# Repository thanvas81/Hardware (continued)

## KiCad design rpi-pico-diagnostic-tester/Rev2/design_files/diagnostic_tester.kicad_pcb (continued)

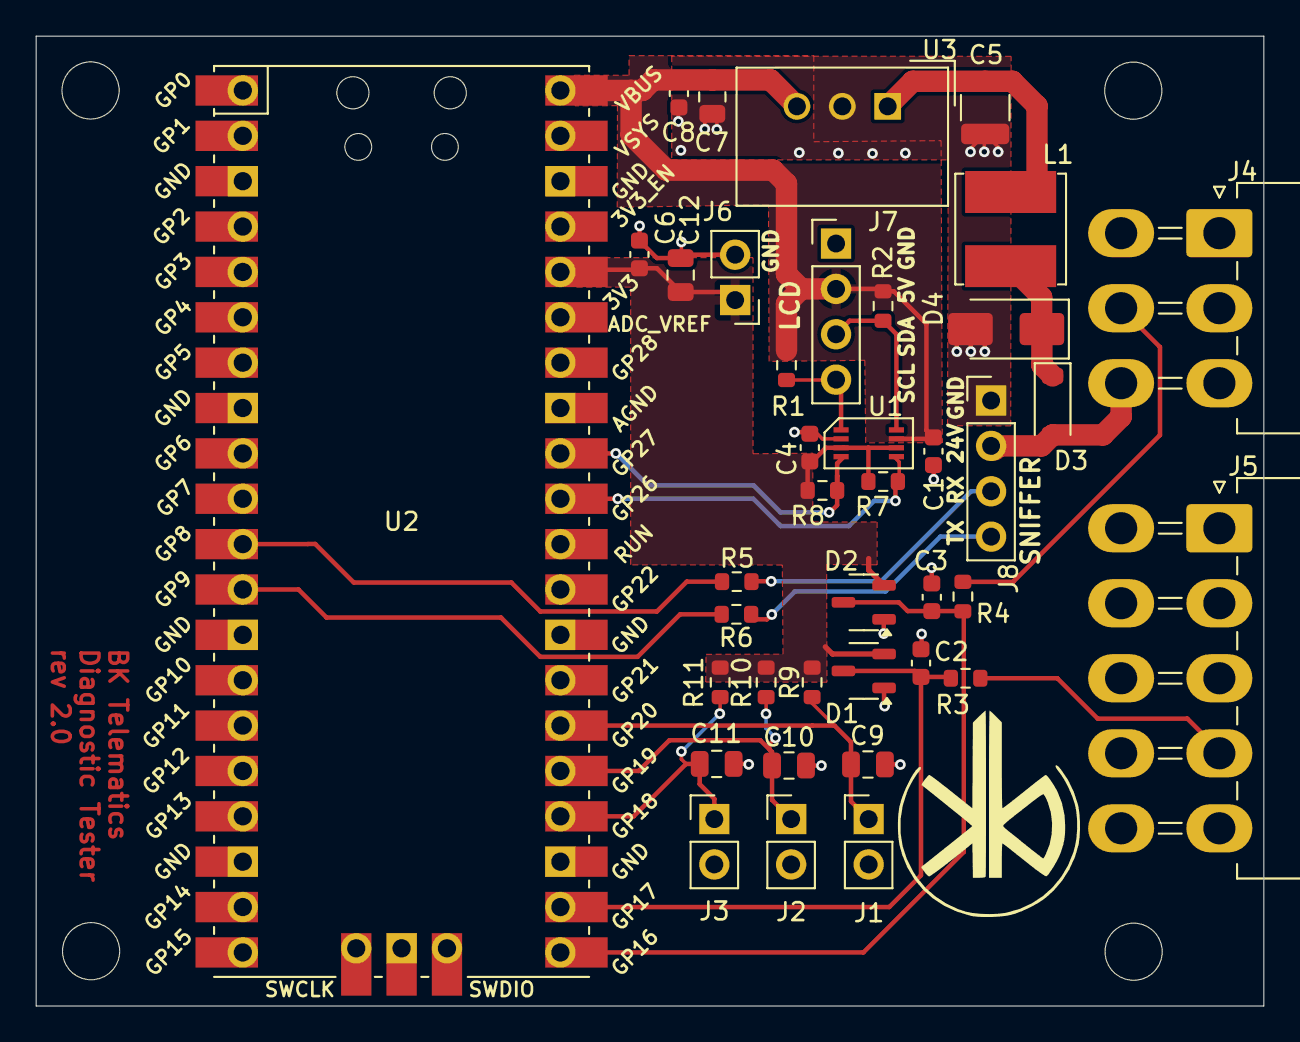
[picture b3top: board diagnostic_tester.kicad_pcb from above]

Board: 2 copper layers, 68.7 x 54.3 mm, 43 parts (0 on the bottom side), 21 nets.

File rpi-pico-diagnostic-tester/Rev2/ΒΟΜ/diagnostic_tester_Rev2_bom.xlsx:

Reference | Qty | Value | Footprint | Description
C1 C4 C6 C8 | 4 | 0.1uF | Capacitor_SMD:C_0603_1608Metric | Unpolarized capacitor, small symbol
C2 C3 | 2 | 100pF | Capacitor_SMD:C_0603_1608Metric | Unpolarized capacitor, small symbol
C5 | 1 | 2.2uF | Capacitor_SMD:C_1210_3225Metric | Unpolarized capacitor, small symbol
C7 C12 | 2 | 10uF | Capacitor_SMD:C_0805_2012Metric | Unpolarized capacitor, small symbol
C9 C10 C11 | 3 | 0.1uF | Capacitor_SMD:C_0805_2012Metric | Unpolarized capacitor, small symbol
D1 D2 | 2 | BAT54SW | Package_TO_SOT_SMD:SOT-323_SC-70 | Vr 30V, If 200mA, Dual schottky barrier diode, in series, SOT-323
D3 | 1 | MBR0540 | Diode_SMD:D_SOD-123 | 40V 0.5A Schottky Power Rectifier Diode, SOD-123
D4 | 1 | SMAJ45A | Diode_SMD:D_SMA | 400W unidirectional Transient Voltage Suppressor, 45.0Vr, SMA(DO-214AC)
H1 H2 H3 H4 | 4 | MountingHole | MountingHole:MountingHole_3.2mm_M3_ISO14580 | Mounting Hole without connection
J1 J2 J3 J6 | 4 | Conn_01x02 | Connector_PinHeader_2.54mm:PinHeader_1x02_P2.54mm_Vertical | Generic connector, single row, 01x02, script generated (kicad-library-utils/sch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
J4 | 1 | Conn_01x06 | Connector_Molex:Molex_Mini-Fit_Jr_5569-06A2_2x03_P4.20mm_Horizontal | Generic connector, single row, 01x06, script generated (kicad-library-utils/sch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
J5 | 1 | Conn_01x10 | Connector_Molex:Molex_Mini-Fit_Jr_5569-10A2_2x05_P4.20mm_Horizontal | Generic connector, single row, 01x10, script generated (kicad-library-utils/sch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
J7 J8 | 2 | Conn_01x04 | Connector_PinHeader_2.54mm:PinHeader_1x04_P2.54mm_Vertical | Generic connector, single row, 01x04, script generated (kicad-library-utils/sch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
L1 | 1 | 47uH | Inductor_SMD:L_Bourns_SRN6045TA | SRN6045HA-470M
R1 R2 R7 R8 | 4 | 2K | Resistor_SMD:R_0603_1608Metric | Resistor, small symbol
R3 R4 R5 R6 | 4 | 27R | Resistor_SMD:R_0603_1608Metric | Resistor, small symbol
R9 R10 R11 | 3 | 100K | Resistor_SMD:R_0603_1608Metric | Resistor, small symbol
U1 | 1 | TXS0102DCU | My Footprints:Package_SO_VSSOP-8_P0.5mm | 2-Bit Bidirectional Voltage-Level Shifter for Open-Drain and Push-Pull Applicat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
U2 | 1 | Pico | My Footprints:RPi_Pico_SMD_TH
U3 | 1 | TSR1-2450E | Converter_DCDC:Converter_DCDC_TRACO_TSR1-xxxxE_THT | 1A step-down regulator, fixed 5V output voltage, 7-36V input voltage, TO-220 co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

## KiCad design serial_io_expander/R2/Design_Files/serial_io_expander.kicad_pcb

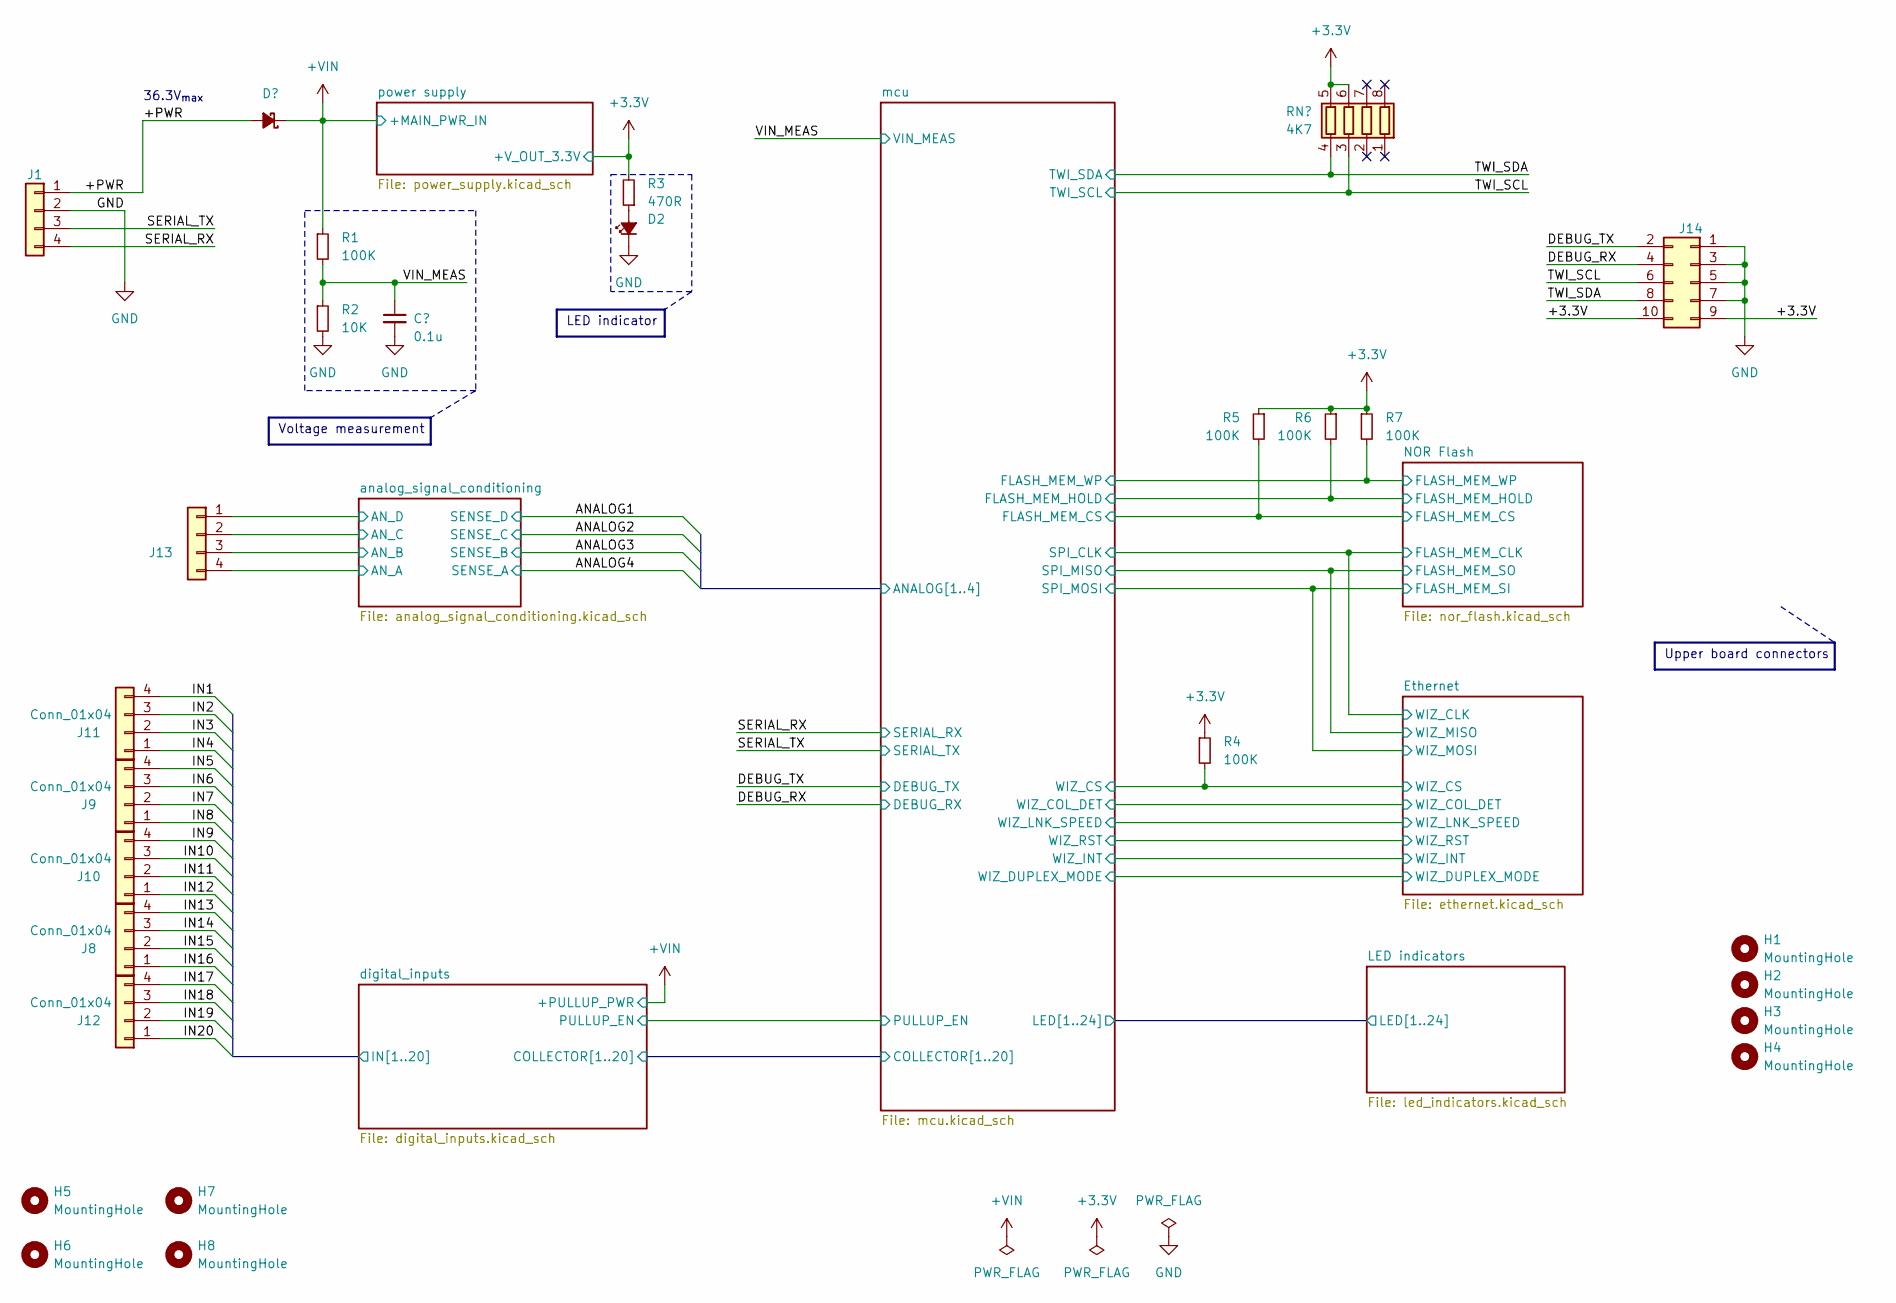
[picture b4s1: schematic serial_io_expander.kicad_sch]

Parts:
C1: 0.1u; C_0603_1608Metric; PartkeeprID 50
D1: SBR3U60P1Q-7; D_PowerDI-123; PartkeeprID 43
D2: LED_Small_Filled; LED_0603_1608Metric
H1, H2, H3, H4: MountingHole; MountingHole_4.3mm_M4
H5, H6, H7, H8: MountingHole; MountingHole_3.2mm_M3_DIN965
J1, J8, J9, J10, J11, J12, J13: Conn_01x04; TerminalBlock_IMO_203001M-4
J14: PinHeader_2x05_P2.54mm_Vertical
R1, R4, R5, R6, R7: 100K; R_0603_1608Metric
R2: 10K; R_0603_1608Metric
R3: 470R; R_0603_1608Metric
RN1: 4K7; R_Array_Concave_4x0603

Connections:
+VIN: D1.1 (K), R1.1; also elsewhere on the board
/+PWR: D1.2 (A), J1.1
/DEBUG_RX: J14.4; also elsewhere on the board
/DEBUG_TX: J14.2; also elsewhere on the board
/Ethernet/WIZ_CS: R4.2; also elsewhere on the board
/NOR Flash/FLASH_MEM_CS: R5.2; also elsewhere on the board
/NOR Flash/FLASH_MEM_HOLD: R6.2; also elsewhere on the board
/NOR Flash/FLASH_MEM_WP: R7.2; also elsewhere on the board
/SERIAL_RX: J1.4; also elsewhere on the board
/SERIAL_TX: J1.3; also elsewhere on the board
/VIN_MEAS: C1.1, R1.2, R2.1; also elsewhere on the board
/analog_signal_conditioning/AN_A: J13.4; also elsewhere on the board
/analog_signal_conditioning/AN_B: J13.3; also elsewhere on the board
/analog_signal_conditioning/AN_C: J13.2; also elsewhere on the board
/analog_signal_conditioning/AN_D: J13.1; also elsewhere on the board
/digital_inputs/IN1: J11.4; also elsewhere on the board
/digital_inputs/IN2: J11.3; also elsewhere on the board
/digital_inputs/IN3: J11.2; also elsewhere on the board
/digital_inputs/IN4: J11.1; also elsewhere on the board
/digital_inputs/IN5: J9.4; also elsewhere on the board
/digital_inputs/IN6: J9.3; also elsewhere on the board
/digital_inputs/IN7: J9.2; also elsewhere on the board
/digital_inputs/IN8: J9.1; also elsewhere on the board
/digital_inputs/IN9: J10.4; also elsewhere on the board
/digital_inputs/IN10: J10.3; also elsewhere on the board
/digital_inputs/IN11: J10.2; also elsewhere on the board
/digital_inputs/IN12: J10.1; also elsewhere on the board
/digital_inputs/IN13: J8.4; also elsewhere on the board
/digital_inputs/IN14: J8.3; also elsewhere on the board
/digital_inputs/IN15: J8.2; also elsewhere on the board
/digital_inputs/IN16: J8.1; also elsewhere on the board
/digital_inputs/IN17: J12.4; also elsewhere on the board
/digital_inputs/IN18: J12.3; also elsewhere on the board
/digital_inputs/IN19: J12.2; also elsewhere on the board
/digital_inputs/IN20: J12.1; also elsewhere on the board
GND: C1.2, D2.1 (K), J1.2, J14.1, J14.3, J14.5, J14.7, R2.2; also elsewhere on the board
unnamed: D2.2 (A), R3.1

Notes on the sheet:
36.3V_{max}
Voltage measurement
Upper board connectors
LED indicator

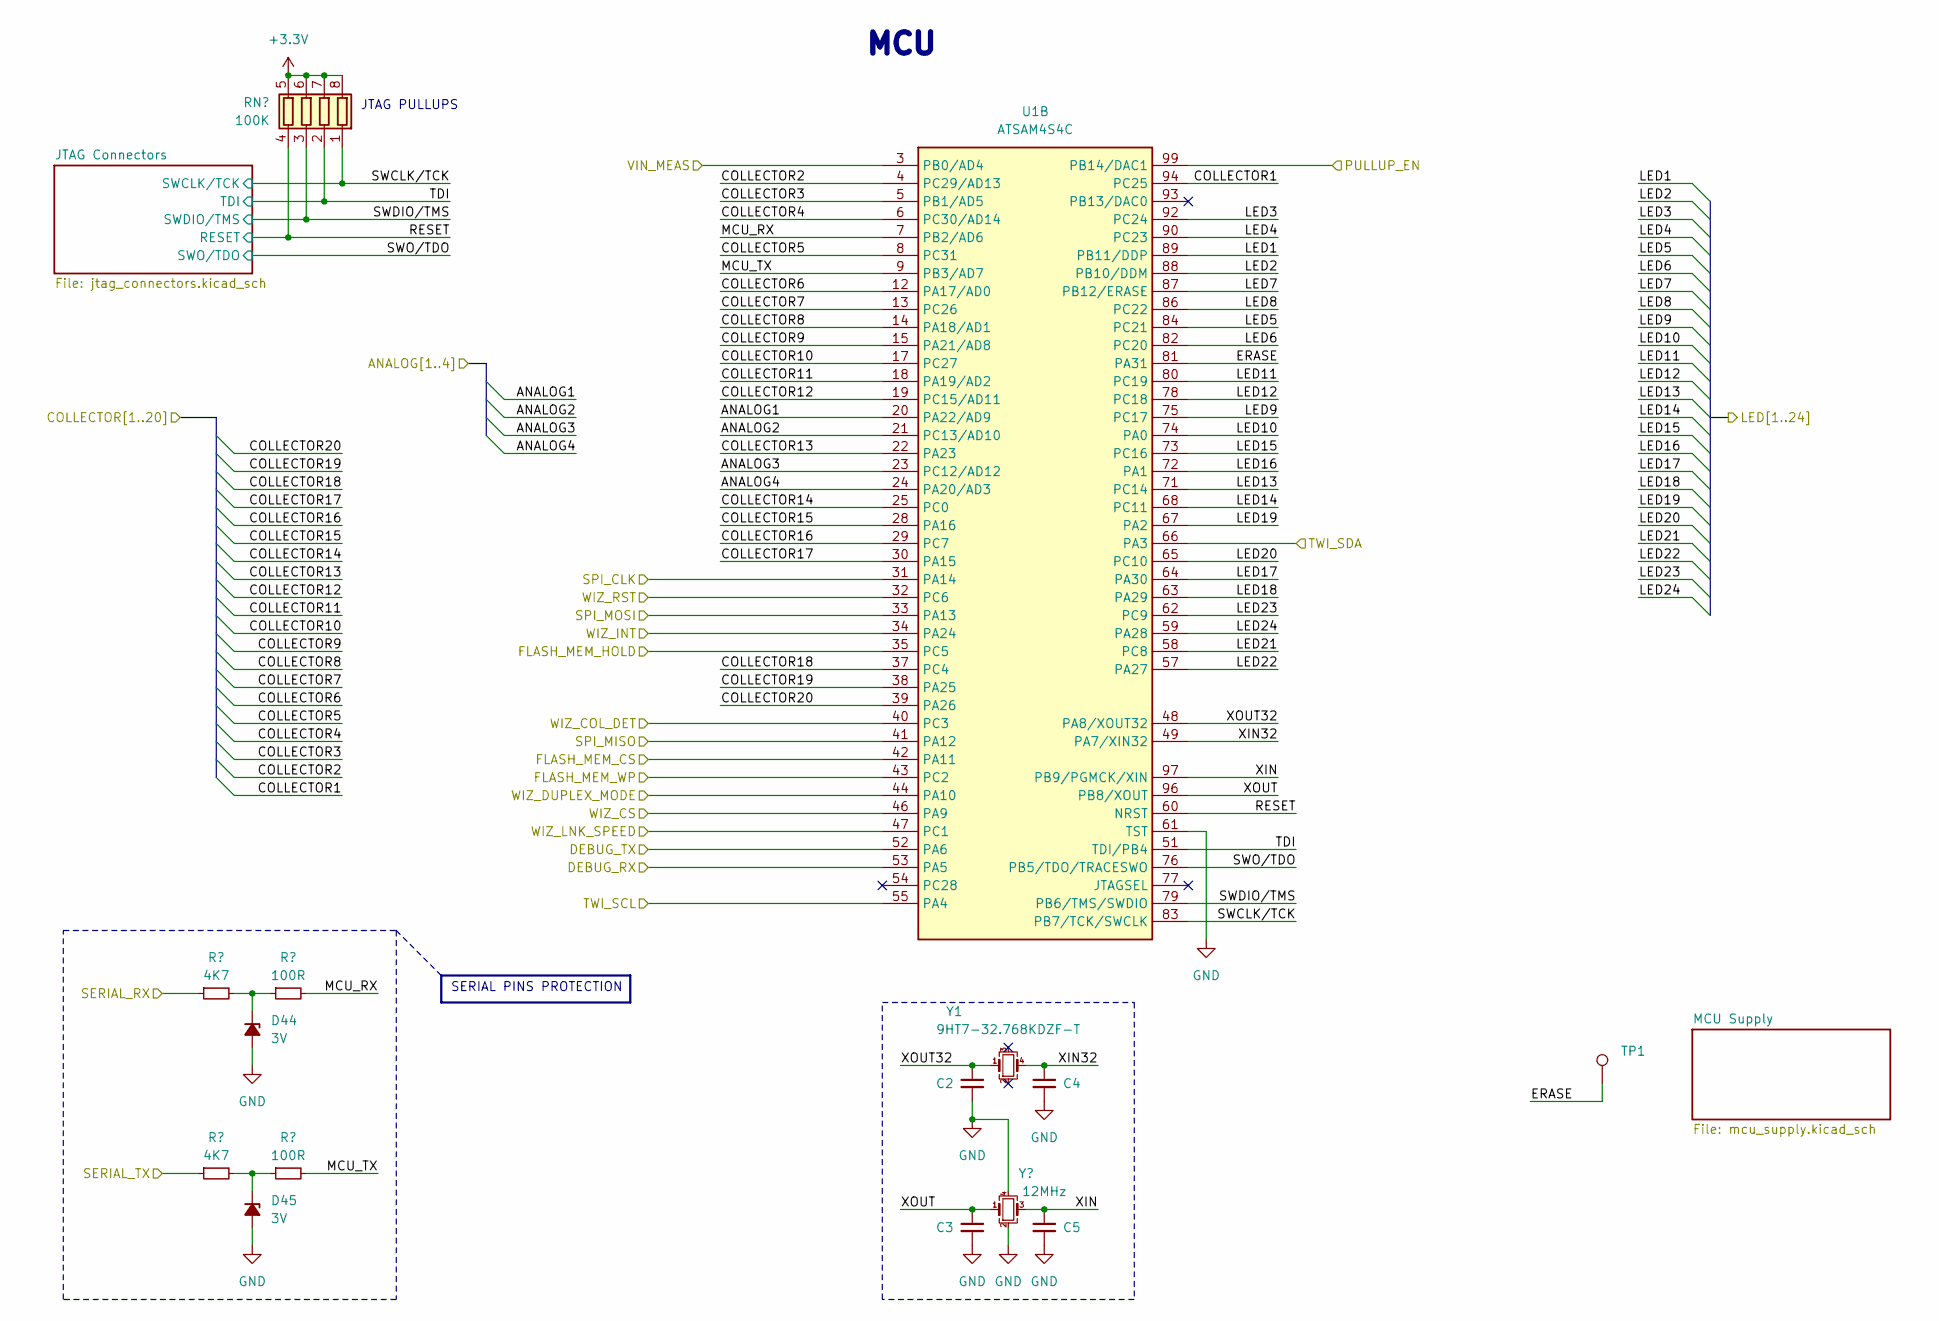
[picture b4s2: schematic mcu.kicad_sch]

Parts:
C2, C3, C4, C5: C_0603_1608Metric
D44, D45: 3V; D_SOD-123; PartkeeprID 75
R72, R73: 4K7; R_0603_1608Metric
R74, R75: 100R; R_0603_1608Metric
RN2: 100K; R_Array_Concave_4x0603
TP1: TestPoint; TestPoint_Pad_D1.5mm
U1: ATSAM4S4C; LQFP-100_14x14mm_P0.5mm
Y1: 9HT7-32.768KDZF-T; Crystal_SMD_TXC_4pin_6.9x1.4
Y2: 12MHz; Crystal_SMD_Abracon_ABM8G-4Pin_3.2x2.5mm

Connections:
/DEBUG_RX: U1.53 (PA5); also elsewhere on the board
/DEBUG_TX: U1.52 (PA6); also elsewhere on the board
/Ethernet/WIZ_CLK: U1.31 (PA14); also elsewhere on the board
/Ethernet/WIZ_COL_DET: U1.40 (PC3); also elsewhere on the board
/Ethernet/WIZ_CS: U1.46 (PA9); also elsewhere on the board
/Ethernet/WIZ_DUPLEX_MODE: U1.44 (PA10); also elsewhere on the board
/Ethernet/WIZ_INT: U1.34 (PA24); also elsewhere on the board
/Ethernet/WIZ_LNK_SPEED: U1.47 (PC1); also elsewhere on the board
/Ethernet/WIZ_MISO: U1.41 (PA12); also elsewhere on the board
/Ethernet/WIZ_MOSI: U1.33 (PA13); also elsewhere on the board
/Ethernet/WIZ_RST: U1.32 (PC6); also elsewhere on the board
/LED indicators/LED1: U1.89 (PB11/DDP); also elsewhere on the board
/LED indicators/LED2: U1.88 (PB10/DDM); also elsewhere on the board
/LED indicators/LED3: U1.92 (PC24); also elsewhere on the board
/LED indicators/LED4: U1.90 (PC23); also elsewhere on the board
/LED indicators/LED5: U1.84 (PC21); also elsewhere on the board
/LED indicators/LED6: U1.82 (PC20); also elsewhere on the board
/LED indicators/LED7: U1.87 (PB12/ERASE); also elsewhere on the board
/LED indicators/LED8: U1.86 (PC22); also elsewhere on the board
/LED indicators/LED9: U1.75 (PC17); also elsewhere on the board
/LED indicators/LED10: U1.74 (PA0); also elsewhere on the board
/LED indicators/LED11: U1.80 (PC19); also elsewhere on the board
/LED indicators/LED12: U1.78 (PC18); also elsewhere on the board
/LED indicators/LED13: U1.71 (PC14); also elsewhere on the board
/LED indicators/LED14: U1.68 (PC11); also elsewhere on the board
/LED indicators/LED15: U1.73 (PC16); also elsewhere on the board
/LED indicators/LED16: U1.72 (PA1); also elsewhere on the board
/LED indicators/LED17: U1.64 (PA30); also elsewhere on the board
/LED indicators/LED18: U1.63 (PA29); also elsewhere on the board
/LED indicators/LED19: U1.67 (PA2); also elsewhere on the board
/LED indicators/LED20: U1.65 (PC10); also elsewhere on the board
/LED indicators/LED21: U1.58 (PC8); also elsewhere on the board
/LED indicators/LED22: U1.57 (PA27); also elsewhere on the board
/LED indicators/LED23: U1.62 (PC9); also elsewhere on the board
/LED indicators/LED24: U1.59 (PA28); also elsewhere on the board
/NOR Flash/FLASH_MEM_CS: U1.42 (PA11); also elsewhere on the board
/NOR Flash/FLASH_MEM_HOLD: U1.35 (PC5); also elsewhere on the board
/NOR Flash/FLASH_MEM_WP: U1.43 (PC2); also elsewhere on the board
/SERIAL_RX: R72.1; also elsewhere on the board
/SERIAL_TX: R73.1; also elsewhere on the board
/VIN_MEAS: U1.3 (PB0/AD4); also elsewhere on the board
/digital_inputs/COLLECTOR1: U1.94 (PC25); also elsewhere on the board
/digital_inputs/COLLECTOR2: U1.4 (PC29/AD13); also elsewhere on the board
/digital_inputs/COLLECTOR3: U1.5 (PB1/AD5); also elsewhere on the board
/digital_inputs/COLLECTOR4: U1.6 (PC30/AD14); also elsewhere on the board
/digital_inputs/COLLECTOR5: U1.8 (PC31); also elsewhere on the board
/digital_inputs/COLLECTOR6: U1.12 (PA17/AD0); also elsewhere on the board
/digital_inputs/COLLECTOR7: U1.13 (PC26); also elsewhere on the board
/digital_inputs/COLLECTOR8: U1.14 (PA18/AD1); also elsewhere on the board
/digital_inputs/COLLECTOR9: U1.15 (PA21/AD8); also elsewhere on the board
/digital_inputs/COLLECTOR10: U1.17 (PC27); also elsewhere on the board
/digital_inputs/COLLECTOR11: U1.18 (PA19/AD2); also elsewhere on the board
/digital_inputs/COLLECTOR12: U1.19 (PC15/AD11); also elsewhere on the board
/digital_inputs/COLLECTOR13: U1.22 (PA23); also elsewhere on the board
/digital_inputs/COLLECTOR14: U1.25 (PC0); also elsewhere on the board
/digital_inputs/COLLECTOR15: U1.28 (PA16); also elsewhere on the board
/digital_inputs/COLLECTOR16: U1.29 (PC7); also elsewhere on the board
/digital_inputs/COLLECTOR17: U1.30 (PA15); also elsewhere on the board
/digital_inputs/COLLECTOR18: U1.37 (PC4); also elsewhere on the board
/digital_inputs/COLLECTOR19: U1.38 (PA25); also elsewhere on the board
/digital_inputs/COLLECTOR20: U1.39 (PA26); also elsewhere on the board
/digital_inputs/PULLUP_EN: U1.99 (PB14/DAC1); also elsewhere on the board
/mcu/ANALOG1: U1.20 (PA22/AD9); also elsewhere on the board
/mcu/ANALOG2: U1.21 (PC13/AD10); also elsewhere on the board
/mcu/ANALOG3: U1.23 (PC12/AD12); also elsewhere on the board
/mcu/ANALOG4: U1.24 (PA20/AD3); also elsewhere on the board
/mcu/MCU Supply/+VDDCORE: U1.11 (VDDOUT), U1.16 (VDDCORE), U1.36 (VDDCORE), U1.56 (VDDCORE), U1.85 (VDDCORE); also elsewhere on the board
/mcu/MCU Supply/+VDDPLL: U1.100 (VDDPLL); also elsewhere on the board
/mcu/MCU_RX: R74.2, U1.7 (PB2/AD6)
/mcu/MCU_TX: R75.2, U1.9 (PB3/AD7)
/mcu/RESET: RN2.4 (R4.1), U1.60 (NRST); also elsewhere on the board
/mcu/SWCLK/TCK: RN2.1 (R1.1), U1.83 (PB7/TCK/SWCLK); also elsewhere on the board
/mcu/SWDIO/TMS: RN2.3 (R3.1), U1.79 (PB6/TMS/SWDIO); also elsewhere on the board
/mcu/SWO/TDO: U1.76 (PB5/TDO/TRACESWO); also elsewhere on the board
/mcu/TDI: RN2.2 (R2.1), U1.51 (TDI/PB4); also elsewhere on the board
/mcu/XIN: C5.1, U1.97 (PB9/PGMCK/XIN), Y2.3
/mcu/XIN32: C4.1, U1.49 (PA7/XIN32), Y1.4
/mcu/XOUT: C3.1, U1.96 (PB8/XOUT), Y2.1
/mcu/XOUT32: C2.1, U1.48 (PA8/XOUT32), Y1.1
GND: C2.2, C3.2, C4.2, C5.2, D44.2 (A), D45.2 (A), U1.2 (GND), U1.26 (GND), U1.45 (GND), U1.61 (TST), U1.70 (GND), U1.95 (GND), Y2.2, Y2.4; also elsewhere on the board
unnamed: D44.1 (K), R72.2, R74.1
unnamed: D45.1 (K), R73.2, R75.1

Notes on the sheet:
JTAG PULLUPS
${TITLE}
SERIAL PINS PROTECTION

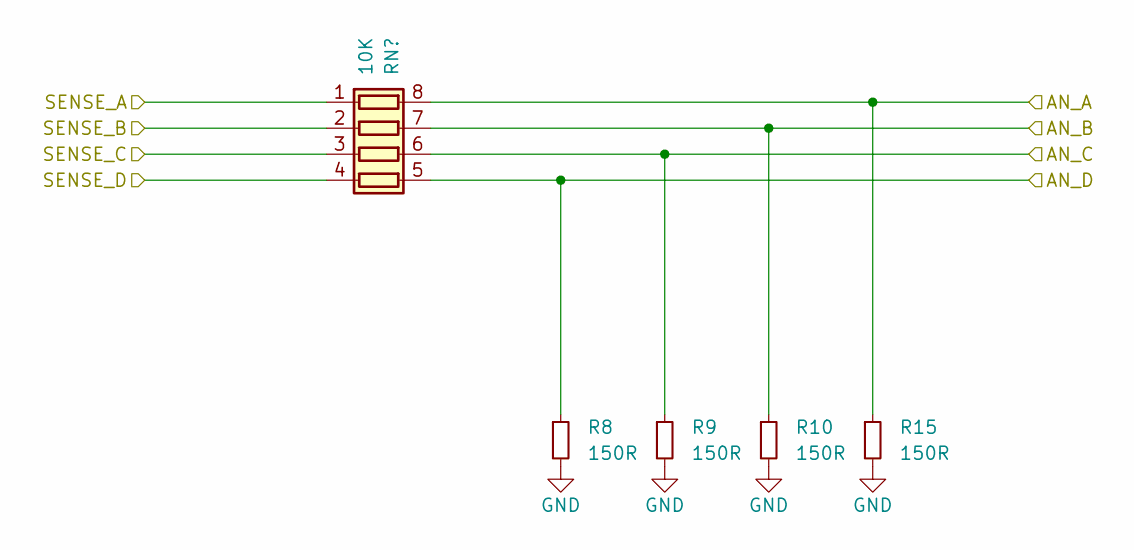
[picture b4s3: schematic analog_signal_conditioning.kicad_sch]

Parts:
R8, R9, R10, R15: 150R; R_2512_6332Metric
RN20: 10K; R_Array_Concave_4x0603

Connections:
/analog_signal_conditioning/AN_A: R15.1, RN20.8 (R1.2); also elsewhere on the board
/analog_signal_conditioning/AN_B: R10.1, RN20.7 (R2.2); also elsewhere on the board
/analog_signal_conditioning/AN_C: R9.1, RN20.6 (R3.2); also elsewhere on the board
/analog_signal_conditioning/AN_D: R8.1, RN20.5 (R4.2); also elsewhere on the board
/mcu/ANALOG1: RN20.4 (R4.1); also elsewhere on the board
/mcu/ANALOG2: RN20.3 (R3.1); also elsewhere on the board
/mcu/ANALOG3: RN20.2 (R2.1); also elsewhere on the board
/mcu/ANALOG4: RN20.1 (R1.1); also elsewhere on the board
GND: R8.2, R9.2, R10.2, R15.2; also elsewhere on the board

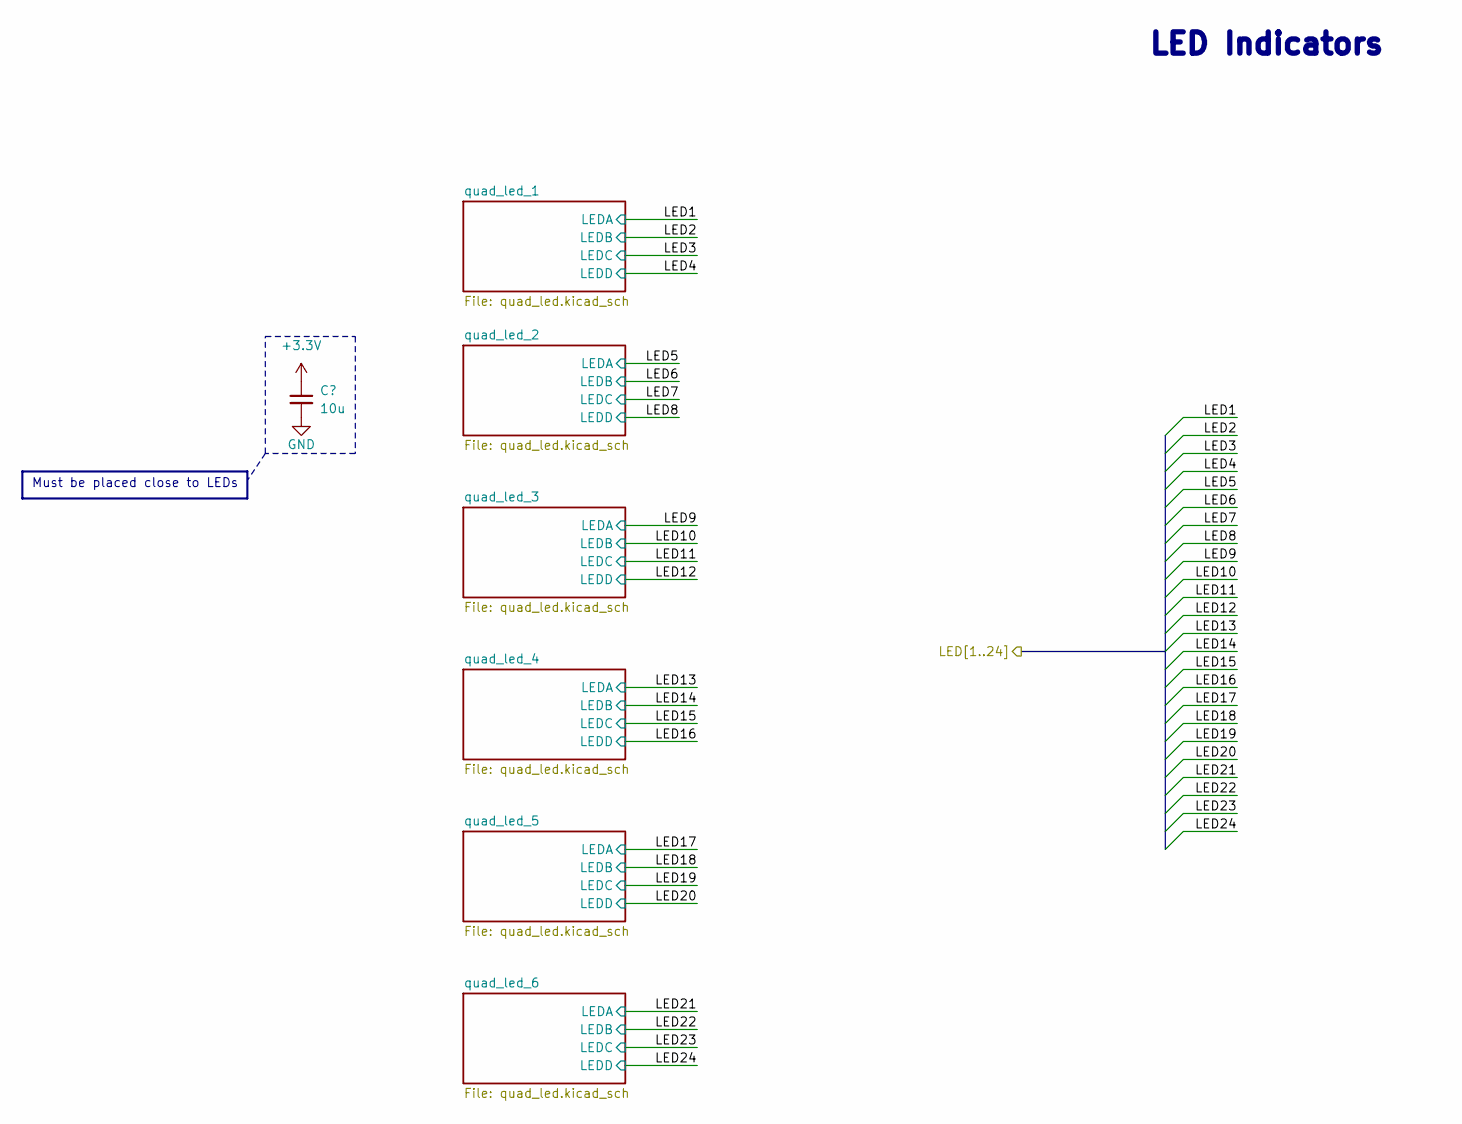
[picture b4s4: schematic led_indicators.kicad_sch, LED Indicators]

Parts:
C13: 10u; C_0805_2012Metric; PartkeeprID 52

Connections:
GND: C13.2; also elsewhere on the board

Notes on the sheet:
Must be placed close to LEDs
${TITLE}

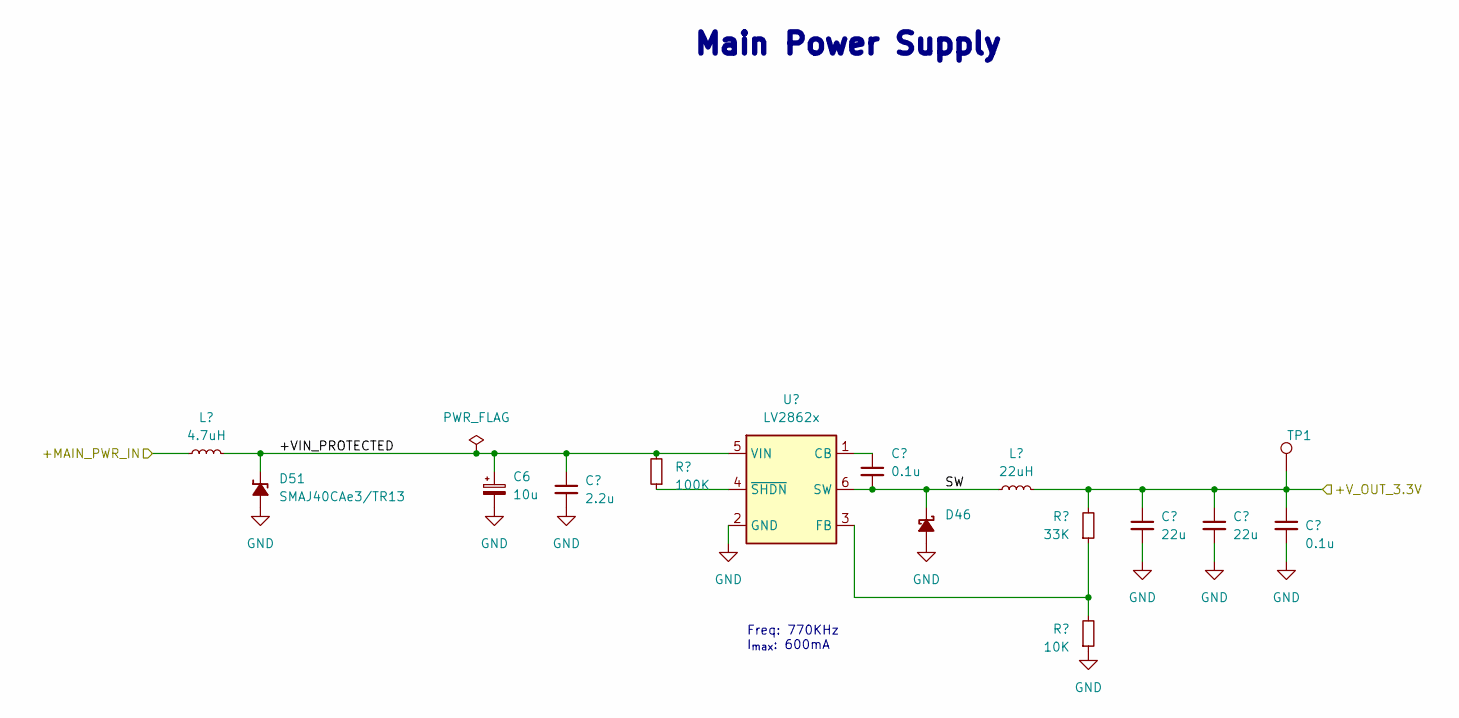
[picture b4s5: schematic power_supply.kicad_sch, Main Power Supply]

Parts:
C6: 10u; CP_Elec_5x5.3; PartkeeprID 41
C7: 2.2u; C_1210_3225Metric; PartkeeprID 42
C8, C11: 0.1u; C_0603_1608Metric; PartkeeprID 50
C9, C10: 22u; C_1210_3225Metric; PartkeeprID 45
D46: SBR3U60P1Q-7; D_PowerDI-123; PartkeeprID 43
D51: SMAJ40CAe3/TR13; D_SMA
L1: 22uH; L_Taiyo-Yuden_NR-50xx; PartkeeprID 44
L5: 4.7uH; L_TDK_VLS252012HBX; PartkeeprID 44
R76: 100K; R_0603_1608Metric; PartkeeprID 47
R77: 33K; R_0603_1608Metric; PartkeeprID 49
R78: 10K; R_0603_1608Metric; PartkeeprID 48
TP1: TestPoint; TestPoint_Pad_D1.5mm
U2: LV2862x; SOT-23-6; PartkeeprID 46

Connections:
+VIN: L5.1; also elsewhere on the board
/power supply/+VIN_PROTECTED: C6.1, C7.1, D51.1 (K), L5.2, R76.2, U2.5 (VIN)
/power supply/SW: C8.2, D46.1 (K), L1.1, U2.6 (SW)
GND: C6.2, C7.2, C9.2, C10.2, C11.2, D46.2 (A), D51.2 (A), R78.1, U2.2 (GND); also elsewhere on the board
unnamed: C8.1, U2.1 (CB)
unnamed: R77.1, R78.2, U2.3 (FB)
unnamed: R76.1, U2.4 (~SHDN)

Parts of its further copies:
TP2: TestPoint; TestPoint_Pad_D1.5mm

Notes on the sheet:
Freq: 770KHz I_{max}: 600mA
${TITLE}

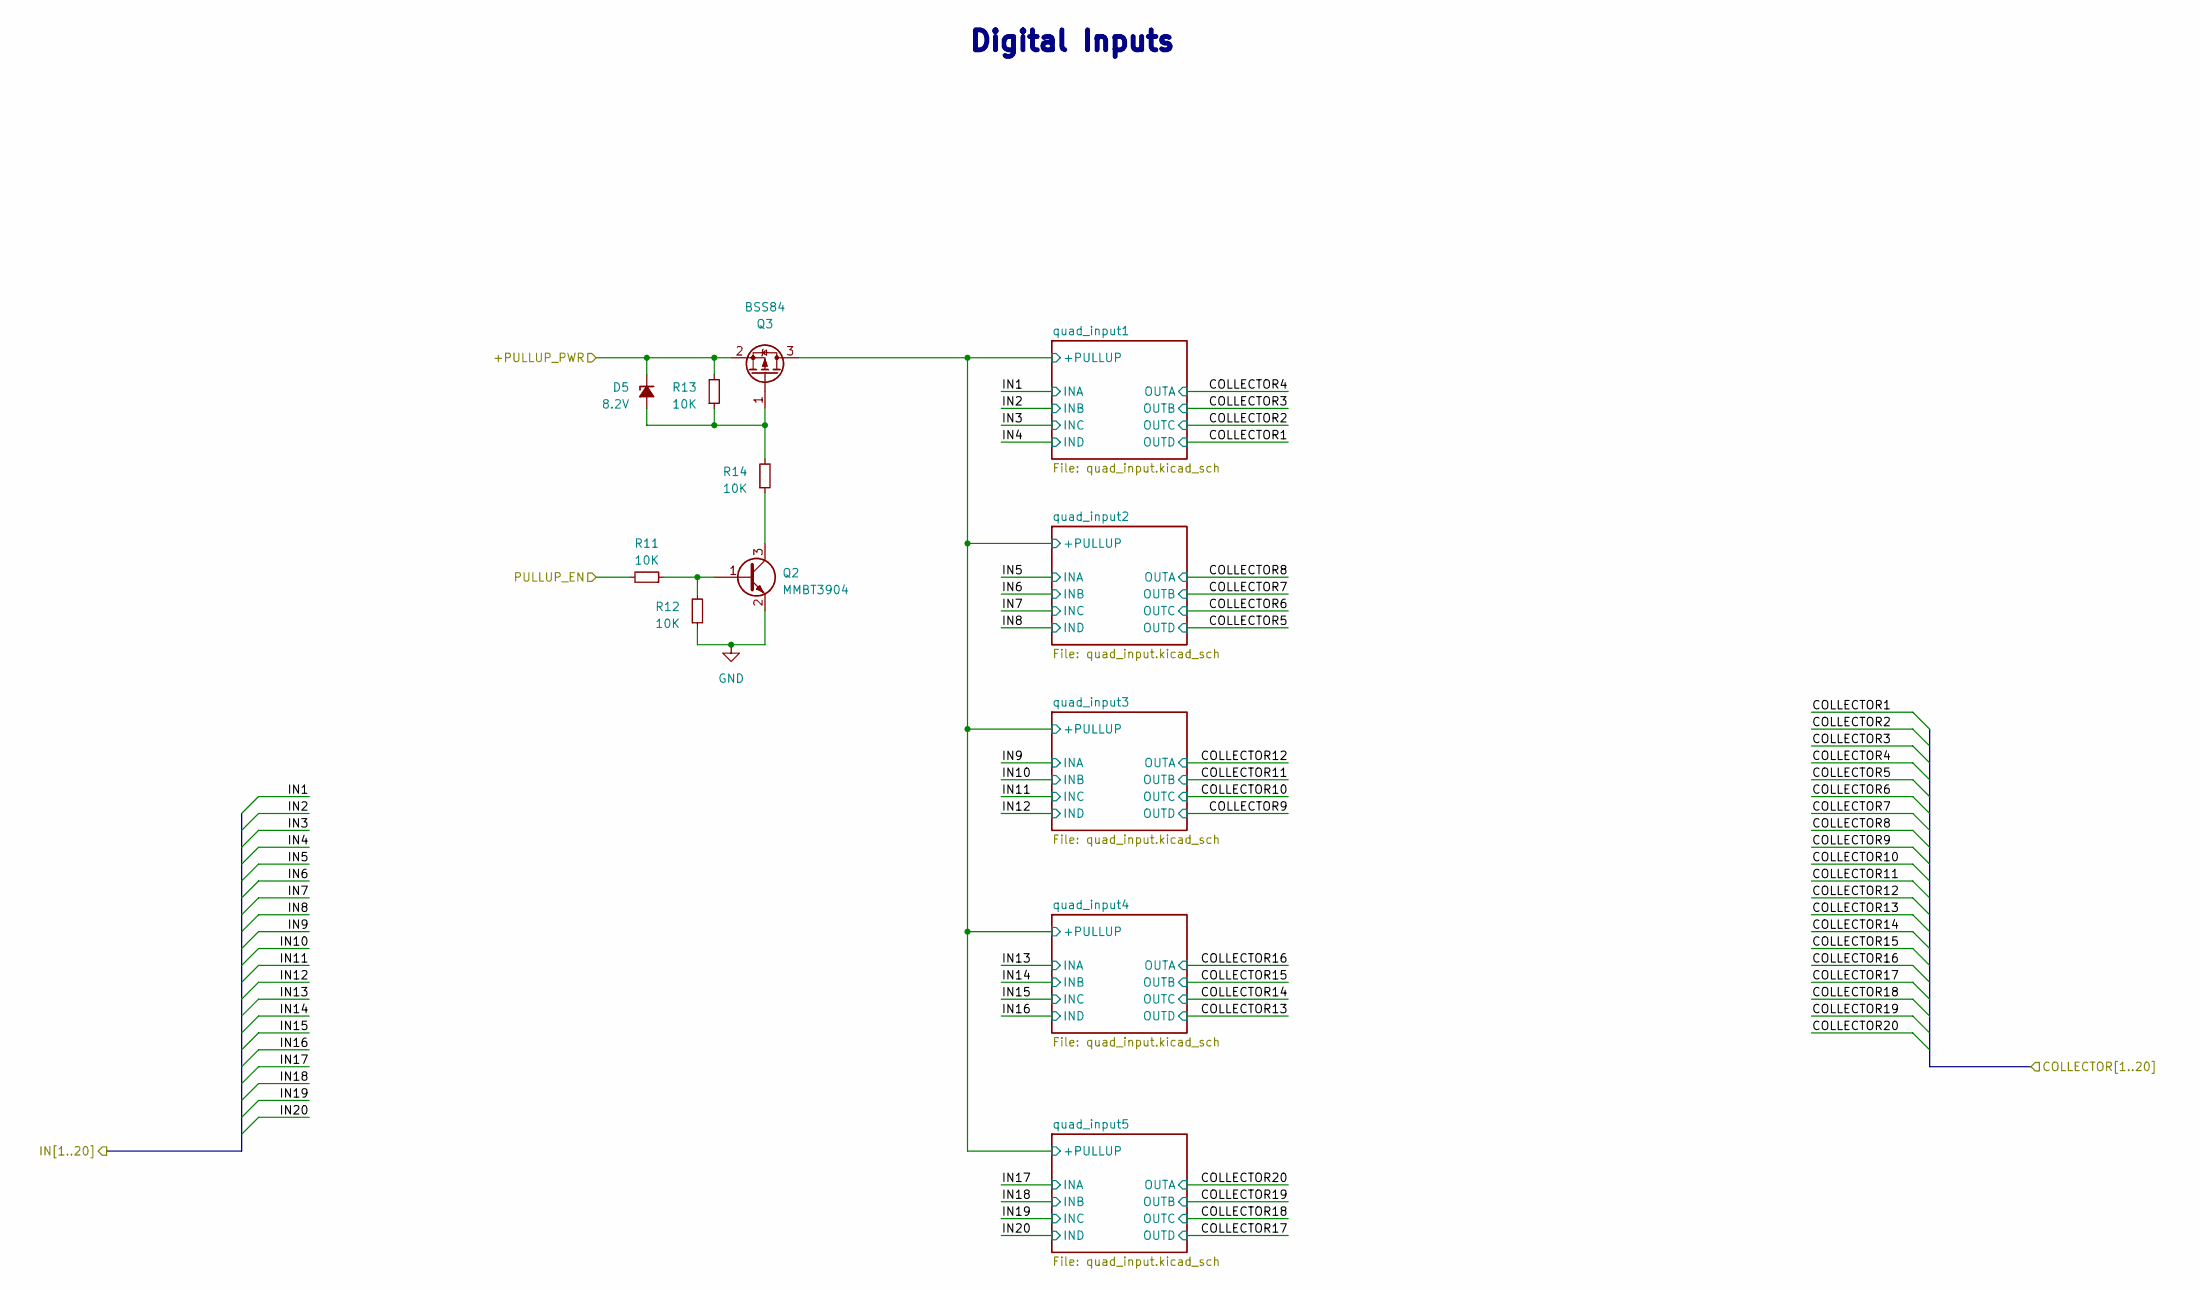
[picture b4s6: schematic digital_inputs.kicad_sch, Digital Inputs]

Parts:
D5: 8.2V; D_SOD-123F; Part No BZT52C8V2-TP
Q2: MMBT3904; SOT-23; Part No MMBT3904-TP
Q3: BSS84; SOT-23; Part No BSS84AK,215
R11, R12, R13, R14: 10K; R_0603_1608Metric

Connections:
+VIN: D5.1 (K), Q3.2 (S), R13.2; also elsewhere on the board
/digital_inputs/PULLUP_EN: R11.2; also elsewhere on the board
/digital_inputs/quad_input1/+PULLUP: Q3.3 (D); also elsewhere on the board
GND: Q2.2 (E), R12.1; also elsewhere on the board
unnamed: D5.2 (A), Q3.1 (G), R13.1, R14.2
unnamed: Q2.1 (B), R11.1, R12.2
unnamed: Q2.3 (C), R14.1

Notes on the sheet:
${TITLE}
